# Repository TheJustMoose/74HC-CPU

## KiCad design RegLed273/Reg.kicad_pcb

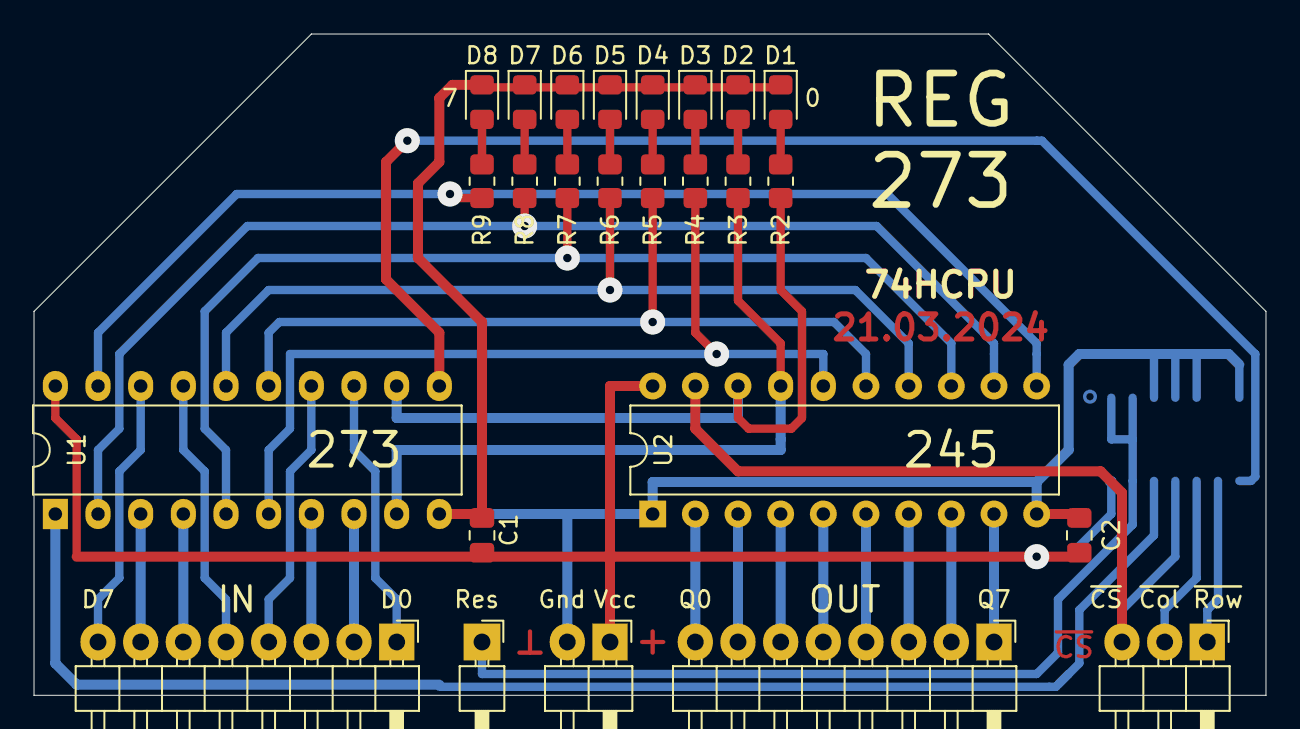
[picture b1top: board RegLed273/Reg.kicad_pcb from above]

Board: 2 copper layers, 73.3 x 39.4 mm, 26 parts (1 on the bottom side), 40 nets.

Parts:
C1, C2: 0.1uF; C_0805_2012Metric_Pad1.18x1.45mm_HandSolder
D1, D2, D3, D4, D5, D6, D7, D8: LED; LED_0805_2012Metric_Pad1.15x1.40mm_HandSolder
J1, J2: Conn_01x08_Male; PinHeader_1x08_P2.54mm_Horizontal
J3: Conn_01x02_Male; PinHeader_1x02_P2.54mm_Horizontal
J4: Conn_01x03_Male; PinHeader_1x03_P2.54mm_Horizontal
J5: Conn_01x01_Male; PinHeader_1x01_P2.54mm_Horizontal
R2, R3, R4, R5, R6, R7, R8, R9: 1k; R_0805_2012Metric_Pad1.20x1.40mm_HandSolder
U1: 74HC273; DIP-20_W7.62mm
U2: 74HC245; DIP-20_W7.62mm
U3: 74LS27; SO-14_3.9x8.65mm_P1.27mm

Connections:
/D0: J1.1, U1.13
/D1: J1.2, U1.8
/D2: J1.3, U1.7
/D3: J1.4, U1.14
/D4: J1.5, U1.17
/D5: J1.6, U1.4
/D6: J1.7, U1.3
/D7: J1.8, U1.18
/L0: R2.1, U1.12, U2.18
/L1: R3.1, U1.9, U2.17
/L2: R4.1, U1.6, U2.16
/L3: R5.1, U1.15, U2.15
/L4: R6.1, U1.16, U2.14
/L5: R7.1, U1.5, U2.13
/L6: R8.1, U1.2, U2.12
/L7: R9.1, U1.19, U2.11
/Q0: J2.8, U2.2
/Q1: J2.7, U2.3
/Q2: J2.6, U2.4
/Q3: J2.5, U2.5
/Q4: J2.4, U2.6
/Q5: J2.3, U2.7
/Q6: J2.2, U2.8
/Q7: J2.1, U2.9
/Res: J5.1, U3.1, U3.2, U3.13
/~CS: J4.3, U2.19, U3.11
/~Col: J4.2, U3.10
/~Row: J4.1, U3.9
GND: C1.2, C2.2, D1.1, D2.1, D3.1, D4.1, D5.1, D6.1, D7.1, D8.1, J3.2, U1.10, U2.1, U2.10, U3.3, U3.4, U3.5, U3.7
unnamed: D1.2, R2.2
unnamed: D2.2, R3.2
unnamed: D3.2, R4.2
unnamed: D4.2, R5.2
unnamed: D5.2, R6.2
unnamed: D6.2, R7.2
unnamed: D7.2, R8.2
unnamed: D8.2, R9.2
unnamed: U1.1, U3.12
unnamed: U1.11, U3.8
VCC: C1.1, C2.1, J3.1, U1.20, U2.20, U3.14

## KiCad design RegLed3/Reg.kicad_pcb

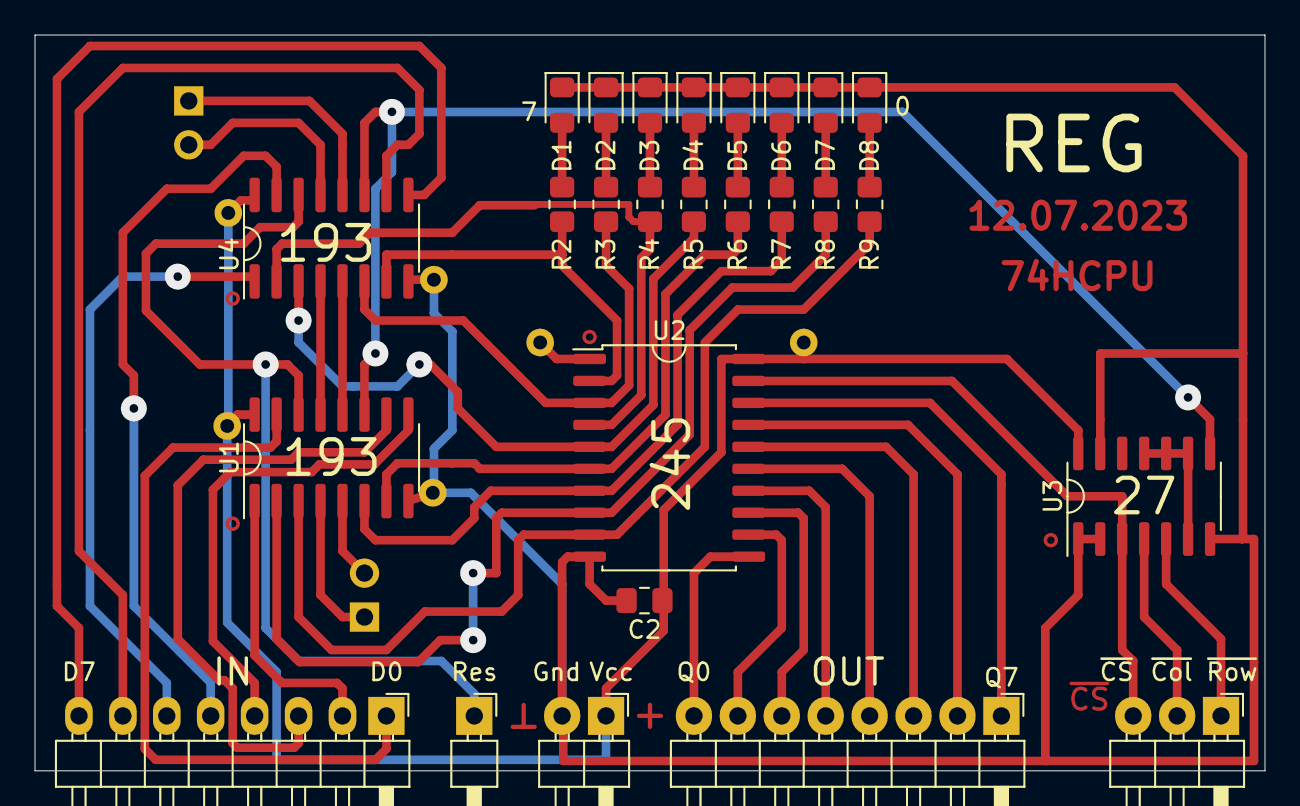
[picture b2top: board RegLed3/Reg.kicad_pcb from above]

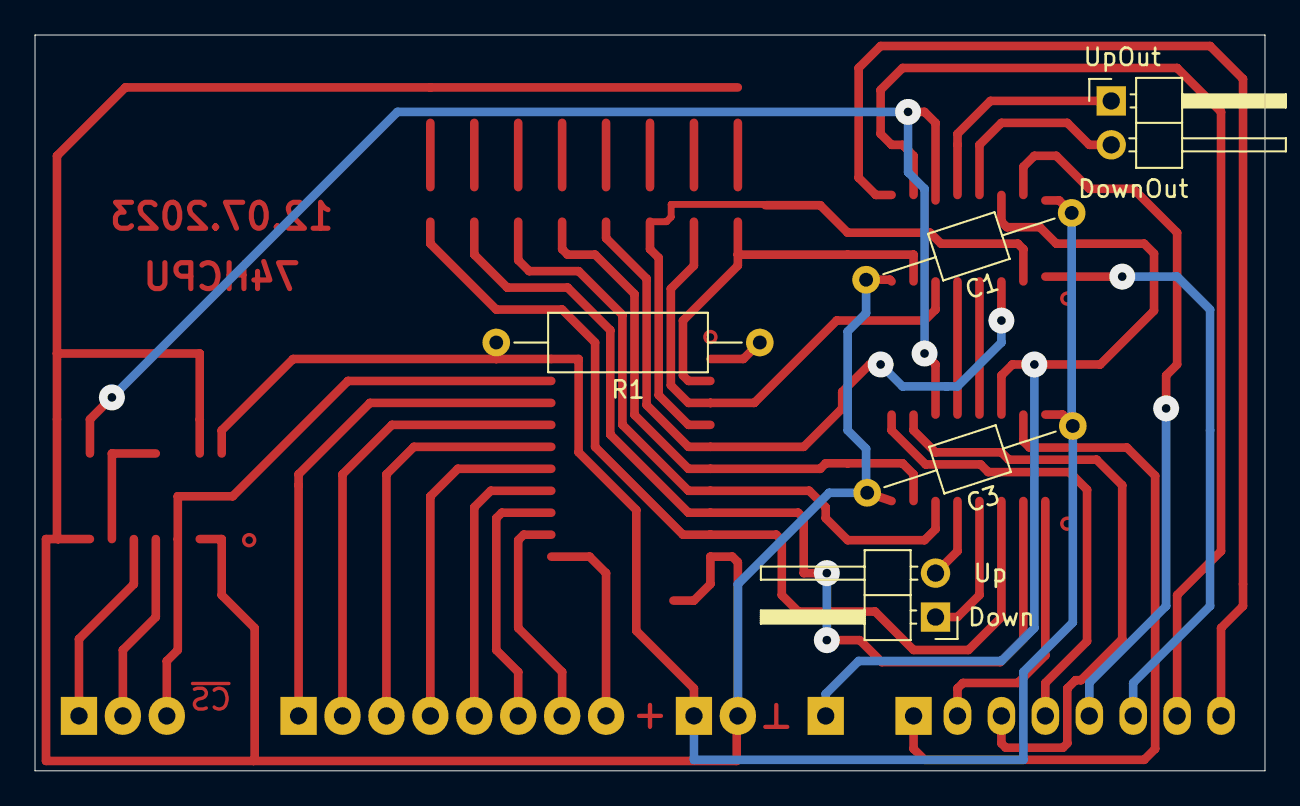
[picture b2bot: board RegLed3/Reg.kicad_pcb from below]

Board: 2 copper layers, 71.1 x 42.5 mm, 31 parts (5 on the bottom side), 47 nets.

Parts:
C1, C3: 0.1uF; C_Axial_L3.8mm_D2.6mm_P12.50mm_Horizontal
C2: 0.1uF; C_0805_2012Metric_Pad1.18x1.45mm_HandSolder
D1, D2, D3, D4, D5, D6, D7, D8: LED; LED_0805_2012Metric_Pad1.15x1.40mm_HandSolder
J1, J2: Conn_01x08_Male; PinHeader_1x08_P2.54mm_Horizontal
J3, J5, J6: Conn_01x02_Male; PinHeader_1x02_P2.54mm_Horizontal
J4: Conn_01x03_Male; PinHeader_1x03_P2.54mm_Horizontal
J7: Conn_01x01_Male; PinHeader_1x01_P2.54mm_Horizontal
R1: 10k; R_Axial_DIN0309_L9.0mm_D3.2mm_P15.24mm_Horizontal
R2, R3, R4, R5, R6, R7, R8, R9: 1k; R_0805_2012Metric_Pad1.20x1.40mm_HandSolder
U1, U4: 74LS193; SOP-16_3.9x9.9mm_P1.27mm
U2: 74HC245; SOP-20_7.5x12.8mm_P1.27mm
U3: 74LS27; SO-14_3.9x8.65mm_P1.27mm

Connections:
/D0: J1.1, U1.15
/D1: J1.2, U1.1
/D2: J1.3, U1.10
/D3: J1.4, U1.9
/D4: J1.5, U4.15
/D5: J1.6, U4.1
/D6: J1.7, U4.10
/D7: J1.8, U4.9
/Down: J6.1, U1.4
/DownLH: U1.13, U4.4
/DownOut: J5.2, U4.13
/L0: R9.1, U1.3, U2.9
/L1: R8.1, U1.2, U2.8
/L2: R7.1, U1.6, U2.7
/L3: R6.1, U1.7, U2.6
/L4: R5.1, U2.5, U4.3
/L5: R4.1, U2.4, U4.2
/L6: R3.1, U2.3, U4.6
/L7: R2.1, U2.2, U4.7
/Q0: J2.8, U2.11
/Q1: J2.7, U2.12
/Q2: J2.6, U2.13
/Q3: J2.5, U2.14
/Q4: J2.4, U2.15
/Q5: J2.3, U2.16
/Q6: J2.2, U2.17
/Q7: J2.1, U2.18
/Res: J7.1, U1.14, U4.14
/Up: J6.2, U1.5
/UpLH: U1.12, U4.5
/UpOut: J5.1, U4.12
/~CS: J4.3, U2.19, U3.3
/~Col: J4.2, U3.4
/~LOAD: U1.11, U3.8, U4.11
/~Row: J4.1, U3.5
GND: C1.2, C2.2, C3.2, D1.1, D2.1, D3.1, D4.1, D5.1, D6.1, D7.1, D8.1, J3.2, U1.8, U2.10, U3.1, U3.2, U3.7, U3.13, U4.8
unnamed: D1.2, R2.2
unnamed: D2.2, R3.2
unnamed: D3.2, R4.2
unnamed: D4.2, R5.2
unnamed: D5.2, R6.2
unnamed: D6.2, R7.2
unnamed: D7.2, R8.2
unnamed: D8.2, R9.2
unnamed: R1.1, U2.1
unnamed: U3.6, U3.9, U3.10, U3.11
VCC: C1.1, C2.1, C3.1, J3.1, R1.2, U1.16, U2.20, U3.14, U4.16

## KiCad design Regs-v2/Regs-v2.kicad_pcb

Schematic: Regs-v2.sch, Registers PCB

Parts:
C1: 1uF; C_Disc_D5.0mm_W2.5mm_P5.00mm
C2, C3, C4: 1uF; C_0805_2012Metric_Pad1.18x1.45mm_HandSolder
D1, D2, D3, D4, D5, D6, D7, D8, D9, D10, D11, D12, D13, D14, D15, D16, D17, D18, D19, D20, D21, D22, D23, D24, D25, D26, D27, D28, D29, D30, D31, D32, D33, D34, D35, D36, D37, D38, D39, D40, D41, D42, D43, D44, D45, D46, D47, D48, D49, D50, D51, D52, D53, D54, D55, D56, D57, D58, D59, D60, D61, D62, D63, D64, D65, D66: LED; LED_Rectangular_W5.0mm_H2.0mm
H1, H2, H3, H4, H5: MountingHole; MountingHole_3.2mm_M3
J1, J2, J3, J4, J5, J6, J7, J8, J10, J13: Conn_01x08_Male; PinHeader_1x08_P2.54mm_Vertical
J9: Conn_01x03_Male; PinHeader_1x03_P2.54mm_Vertical
J11, J12, J16: Conn_01x01_Male; PinHeader_1x01_P2.54mm_Vertical
J14: Conn_01x02_Male; PinHeader_1x02_P2.54mm_Vertical
J15: Screw_Terminal_01x02; TerminalBlock_Phoenix_MKDS-1,5-2_1x02_P5.00mm_Horizontal
R1, R5, R7: 10k; R_Axial_DIN0207_L6.3mm_D2.5mm_P7.62mm_Horizontal
R4, R6: 1k; R_Axial_DIN0207_L6.3mm_D2.5mm_P7.62mm_Horizontal
RN1, RN2, RN3, RN4, RN5, RN6, RN7, RN8: R_Network08; R_Array_SIP9
SW1, SW2: SW_Push; SW_PUSH_6mm_H5mm
U1, U2, U3, U4, U5, U6, U7, U8, U9, U10, U11, U12, U13, U14: REG
U15: 74HC02; DIP-14_W7.62mm_Socket
U16: 74LS139; DIP-16_W7.62mm_Socket
U17: 74HC00; DIP-14_W7.62mm_Socket
U18: 74LS10; DIP-14_W7.62mm_Socket

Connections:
/8\16: J11.1, R1.1, U15.8, U15.12
/DH0: J13.1, U8.1 (D0), U9.1 (D0), U10.1 (D0), U11.1 (D0), U12.1 (D0), U13.1 (D0), U14.1 (D0); also elsewhere on the board
/DH1: J13.2, U8.2 (D1), U9.2 (D1), U10.2 (D1), U11.2 (D1), U12.2 (D1), U13.2 (D1), U14.2 (D1); also elsewhere on the board
/DH2: J13.3, U8.3 (D2), U9.3 (D2), U10.3 (D2), U11.3 (D2), U12.3 (D2), U13.3 (D2), U14.3 (D2); also elsewhere on the board
/DH3: J13.4, U8.4 (D3), U9.4 (D3), U10.4 (D3), U11.4 (D3), U12.4 (D3), U13.4 (D3), U14.4 (D3); also elsewhere on the board
/DH4: J13.5, U8.5 (D4), U9.5 (D4), U10.5 (D4), U11.5 (D4), U12.5 (D4), U13.5 (D4), U14.5 (D4); also elsewhere on the board
/DH5: J13.6, U8.6 (D5), U9.6 (D5), U10.6 (D5), U11.6 (D5), U12.6 (D5), U13.6 (D5), U14.6 (D5); also elsewhere on the board
/DH6: J13.7, U8.7 (D6), U9.7 (D6), U10.7 (D6), U11.7 (D6), U12.7 (D6), U13.7 (D6), U14.7 (D6); also elsewhere on the board
/DH7: J13.8, U8.8 (D7), U9.8 (D7), U10.8 (D7), U11.8 (D7), U12.8 (D7), U13.8 (D7), U14.8 (D7); also elsewhere on the board
/DL1: J10.2, J12.2, U1.2 (D1), U2.2 (D1), U3.2 (D1), U4.2 (D1), U5.2 (D1), U6.2 (D1), U7.2 (D1)
/DL2: J10.3, J12.3, U1.3 (D2), U2.3 (D2), U3.3 (D2), U4.3 (D2), U5.3 (D2), U6.3 (D2), U7.3 (D2)
/DL3: J10.4, J12.4, U1.4 (D3), U2.4 (D3), U3.4 (D3), U4.4 (D3), U5.4 (D3), U6.4 (D3), U7.4 (D3)
/DL4: J10.5, J12.5, U1.5 (D4), U2.5 (D4), U3.5 (D4), U4.5 (D4), U5.5 (D4), U6.5 (D4), U7.5 (D4)
/DL5: J10.6, J12.6, U1.6 (D5), U2.6 (D5), U3.6 (D5), U4.6 (D5), U5.6 (D5), U6.6 (D5), U7.6 (D5)
/DL6: J10.7, J12.7, U1.7 (D6), U2.7 (D6), U3.7 (D6), U4.7 (D6), U5.7 (D6), U6.7 (D6), U7.7 (D6)
/DL7: J10.8, J12.8, U1.8 (D7), U2.8 (D7), U3.8 (D7), U4.8 (D7), U5.8 (D7), U6.8 (D7), U7.8 (D7)
/Latch: J16.1, U15.2, U15.3
/R0.0: D1.2 (A), J1.1, U1.18 (Q0)
/R0.1: D2.2 (A), J1.2, U1.17 (Q1)
/R0.2: D3.2 (A), J1.3, U1.16 (Q2)
/R0.3: D4.2 (A), J1.4, U1.15 (Q3)
/R0.4: D5.2 (A), J1.5, U1.14 (Q4)
/R0.5: D6.2 (A), J1.6, U1.13 (Q5)
/R0.6: D7.2 (A), J1.7, U1.12 (Q6)
/R0.7: D8.2 (A), J1.8, U1.11 (Q7)
/R1.0: D33.2 (A), J5.1, U8.18 (Q0)
/R1.1: D34.2 (A), J5.2, U8.17 (Q1)
/R1.2: D35.2 (A), J5.3, U8.16 (Q2)
/R1.3: D36.2 (A), J5.4, U8.15 (Q3)
/R1.4: D37.2 (A), J5.5, U8.14 (Q4)
/R1.5: D38.2 (A), J5.6, U8.13 (Q5)
/R1.6: D39.2 (A), J5.7, U8.12 (Q6)
/R1.7: D40.2 (A), J5.8, U8.11 (Q7)
/R2.0: D9.2 (A), J2.1, U2.18 (Q0), U3.18 (Q0)
/R2.1: D10.2 (A), J2.2, U2.17 (Q1), U3.17 (Q1)
/R2.2: D11.2 (A), J2.3, U2.16 (Q2), U3.16 (Q2)
/R2.3: D12.2 (A), J2.4, U2.15 (Q3), U3.15 (Q3)
/R2.4: D13.2 (A), J2.5, U2.14 (Q4), U3.14 (Q4)
/R2.5: D14.2 (A), J2.6, U2.13 (Q5), U3.13 (Q5)
/R2.6: D15.2 (A), J2.7, U2.12 (Q6), U3.12 (Q6)
/R2.7: D16.2 (A), J2.8, U2.11 (Q7), U3.11 (Q7)
/R3.0: D41.2 (A), J6.1, U9.18 (Q0), U10.18 (Q0)
/R3.1: D42.2 (A), J6.2, U9.17 (Q1), U10.17 (Q1)
/R3.2: D43.2 (A), J6.3, U9.16 (Q2), U10.16 (Q2)
/R3.3: D44.2 (A), J6.4, U9.15 (Q3), U10.15 (Q3)
/R3.4: D45.2 (A), J6.5, U9.14 (Q4), U10.14 (Q4)
/R3.5: D46.2 (A), J6.6, U9.13 (Q5), U10.13 (Q5)
/R3.6: D47.2 (A), J6.7, U9.12 (Q6), U10.12 (Q6)
/R3.7: D48.2 (A), J6.8, U9.11 (Q7), U10.11 (Q7)
/R4.0: D17.2 (A), J3.1, U4.18 (Q0), U5.18 (Q0)
/R4.1: D18.2 (A), J3.2, U4.17 (Q1), U5.17 (Q1)
/R4.2: D19.2 (A), J3.3, U4.16 (Q2), U5.16 (Q2)
/R4.3: D20.2 (A), J3.4, U4.15 (Q3), U5.15 (Q3)
/R4.4: D21.2 (A), J3.5, U4.14 (Q4), U5.14 (Q4)
/R4.5: D22.2 (A), J3.6, U4.13 (Q5), U5.13 (Q5)
/R4.6: D23.2 (A), J3.7, U4.12 (Q6), U5.12 (Q6)
/R4.7: D24.2 (A), J3.8, U4.11 (Q7), U5.11 (Q7)
/R5.0: D49.2 (A), J7.1, U11.18 (Q0), U12.18 (Q0)
/R5.1: D50.2 (A), J7.2, U11.17 (Q1), U12.17 (Q1)
/R5.2: D51.2 (A), J7.3, U11.16 (Q2), U12.16 (Q2)
/R5.3: D52.2 (A), J7.4, U11.15 (Q3), U12.15 (Q3)
/R5.4: D53.2 (A), J7.5, U11.14 (Q4), U12.14 (Q4)
/R5.5: D54.2 (A), J7.6, U11.13 (Q5), U12.13 (Q5)
/R5.6: D55.2 (A), J7.7, U11.12 (Q6), U12.12 (Q6)
/R5.7: D56.2 (A), J7.8, U11.11 (Q7), U12.11 (Q7)
/R6.0: D25.2 (A), J4.1, U6.18 (Q0), U7.18 (Q0)
/R6.1: D26.2 (A), J4.2, U6.17 (Q1), U7.17 (Q1)
/R6.2: D27.2 (A), J4.3, U6.16 (Q2), U7.16 (Q2)
/R6.3: D28.2 (A), J4.4, U6.15 (Q3), U7.15 (Q3)
/R6.4: D29.2 (A), J4.5, U6.14 (Q4), U7.14 (Q4)
/R6.5: D30.2 (A), J4.6, U6.13 (Q5), U7.13 (Q5)
/R6.6: D31.2 (A), J4.7, U6.12 (Q6), U7.12 (Q6)
/R6.7: D32.2 (A), J4.8, U6.11 (Q7), U7.11 (Q7)
/R7.0: D57.2 (A), J8.1, U13.18 (Q0), U14.18 (Q0)
/R7.1: D58.2 (A), J8.2, U13.17 (Q1), U14.17 (Q1)
/R7.2: D59.2 (A), J8.3, U13.16 (Q2), U14.16 (Q2)
/R7.3: D60.2 (A), J8.4, U13.15 (Q3), U14.15 (Q3)
/R7.4: D61.2 (A), J8.5, U13.14 (Q4), U14.14 (Q4)
/R7.5: D62.2 (A), J8.6, U13.13 (Q5), U14.13 (Q5)
/R7.6: D63.2 (A), J8.7, U13.12 (Q6), U14.12 (Q6)
/R7.7: D64.2 (A), J8.8, U13.11 (Q7), U14.11 (Q7)
/Reg[0]: J9.1, U15.5, U15.6, U15.9
/Reg[1]: J9.2, U16.2 (A0)
/Reg[2]: J9.3, U16.3 (A1)
/~Col0: U1.20 (~Col), U8.20 (~Col), U16.4 (O0)
/~Col1: U2.20 (~Col), U3.20 (~Col), U9.20 (~Col), U10.20 (~Col), U16.5 (O1)
/~Col2: U4.20 (~Col), U5.20 (~Col), U11.20 (~Col), U12.20 (~Col), U16.6 (O2)
/~Col3: U6.20 (~Col), U7.20 (~Col), U13.20 (~Col), U14.20 (~Col), U16.7 (O3)
/~RowH: U8.21 (~Row), U9.21 (~Row), U10.21 (~Row), U11.21 (~Row), U12.21 (~Row), U13.21 (~Row), U14.21 (~Row), U15.10
/~RowL: U1.21 (~Row), U2.21 (~Row), U3.21 (~Row), U4.21 (~Row), U5.21 (~Row), U6.21 (~Row), U7.21 (~Row), U15.13
GND: C1.2, C2.2, C3.2, C4.2, J15.2, R1.2, RN1.1 (common), RN2.1 (common), RN3.1 (common), RN4.1 (common), RN5.1 (common), RN6.1 (common), RN7.1 (common), RN8.1 (common), U1.9 (Gnd), U1.19 (~CS), U2.9 (Gnd), U3.9 (Gnd), U4.9 (Gnd), U5.9 (Gnd), U6.9 (Gnd), U7.9 (Gnd), U8.9 (Gnd), U8.19 (~CS), U9.9 (Gnd), U10.9 (Gnd), U11.9 (Gnd), U12.9 (Gnd), U13.9 (Gnd), U14.9 (Gnd), U15.7 (GND), U16.8 (GND); also elsewhere on the board
unnamed: C1.1, R7.2
unnamed: D1.1 (K), RN1.9 (R8)
unnamed: D2.1 (K), RN1.8 (R7)
unnamed: D3.1 (K), RN1.7 (R6)
unnamed: D4.1 (K), RN1.6 (R5)
unnamed: D5.1 (K), RN1.5 (R4)
unnamed: D6.1 (K), RN1.4 (R3)
unnamed: D7.1 (K), RN1.3 (R2)
unnamed: D8.1 (K), RN1.2 (R1)
unnamed: D9.1 (K), RN2.9 (R8)
unnamed: D10.1 (K), RN2.8 (R7)
unnamed: D11.1 (K), RN2.7 (R6)
unnamed: D12.1 (K), RN2.6 (R5)
unnamed: D13.1 (K), RN2.5 (R4)
unnamed: D14.1 (K), RN2.4 (R3)
unnamed: D15.1 (K), RN2.3 (R2)
unnamed: D16.1 (K), RN2.2 (R1)
unnamed: D17.1 (K), RN3.9 (R8)
unnamed: D18.1 (K), RN3.8 (R7)
unnamed: D19.1 (K), RN3.7 (R6)
unnamed: D20.1 (K), RN3.6 (R5)
unnamed: D21.1 (K), RN3.5 (R4)
unnamed: D22.1 (K), RN3.4 (R3)
unnamed: D23.1 (K), RN3.3 (R2)
unnamed: D24.1 (K), RN3.2 (R1)
unnamed: D25.1 (K), RN4.9 (R8)
unnamed: D26.1 (K), RN4.8 (R7)
unnamed: D27.1 (K), RN4.7 (R6)
unnamed: D28.1 (K), RN4.6 (R5)
unnamed: D29.1 (K), RN4.5 (R4)
unnamed: D30.1 (K), RN4.4 (R3)
unnamed: D31.1 (K), RN4.3 (R2)
unnamed: D32.1 (K), RN4.2 (R1)
unnamed: D33.1 (K), RN5.9 (R8)
unnamed: D34.1 (K), RN5.8 (R7)
unnamed: D35.1 (K), RN5.7 (R6)
unnamed: D36.1 (K), RN5.6 (R5)
unnamed: D37.1 (K), RN5.5 (R4)
unnamed: D38.1 (K), RN5.4 (R3)
unnamed: D39.1 (K), RN5.3 (R2)
unnamed: D40.1 (K), RN5.2 (R1)
unnamed: D41.1 (K), RN6.9 (R8)
unnamed: D42.1 (K), RN6.8 (R7)
unnamed: D43.1 (K), RN6.7 (R6)
unnamed: D44.1 (K), RN6.6 (R5)
unnamed: D45.1 (K), RN6.5 (R4)
unnamed: D46.1 (K), RN6.4 (R3)
unnamed: D47.1 (K), RN6.3 (R2)
unnamed: D48.1 (K), RN6.2 (R1)
unnamed: D49.1 (K), RN7.9 (R8)
unnamed: D50.1 (K), RN7.8 (R7)
unnamed: D51.1 (K), RN7.7 (R6)
unnamed: D52.1 (K), RN7.6 (R5)
unnamed: D53.1 (K), RN7.5 (R4)
unnamed: D54.1 (K), RN7.4 (R3)
unnamed: D55.1 (K), RN7.3 (R2)
unnamed: D56.1 (K), RN7.2 (R1)
unnamed: D57.1 (K), RN8.9 (R8)
unnamed: D58.1 (K), RN8.8 (R7)
unnamed: D59.1 (K), RN8.7 (R6)
unnamed: D60.1 (K), RN8.6 (R5)
unnamed: D61.1 (K), RN8.5 (R4)
unnamed: D62.1 (K), RN8.4 (R3)
unnamed: D63.1 (K), RN8.3 (R2)
unnamed: D64.1 (K), RN8.2 (R1)
unnamed: D65.2 (A), R4.2
unnamed: D66.2 (A), R6.2
unnamed: U15.1, U16.1 (E)
unnamed: U15.4, U15.11
VCC: C2.1, C3.1, C4.1, J15.1, R4.1, R5.1, R6.1, R7.1, U1.10 (Vcc), U2.10 (Vcc), U3.10 (Vcc), U4.10 (Vcc), U5.10 (Vcc), U6.10 (Vcc), U7.10 (Vcc), U8.10 (Vcc), U9.10 (Vcc), U10.10 (Vcc), U11.10 (Vcc), U12.10 (Vcc), U13.10 (Vcc), U14.10 (Vcc), U15.14 (VCC), U16.16 (VCC); also elsewhere on the board

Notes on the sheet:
Bank0
Bank1

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
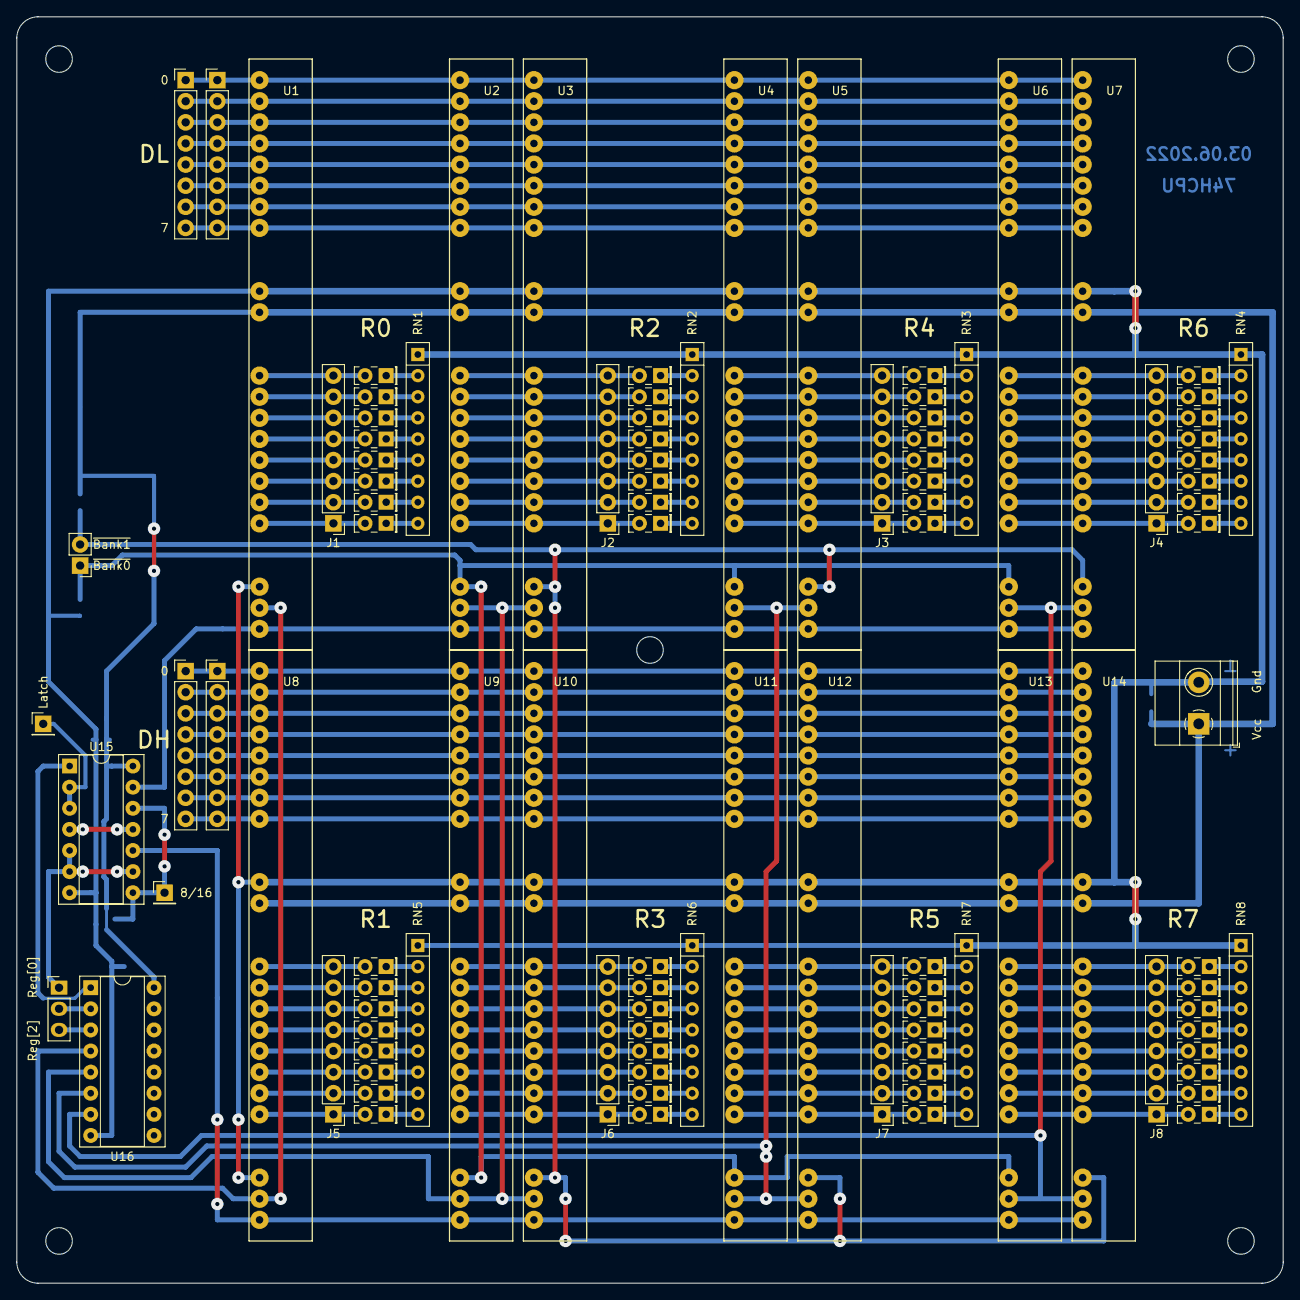
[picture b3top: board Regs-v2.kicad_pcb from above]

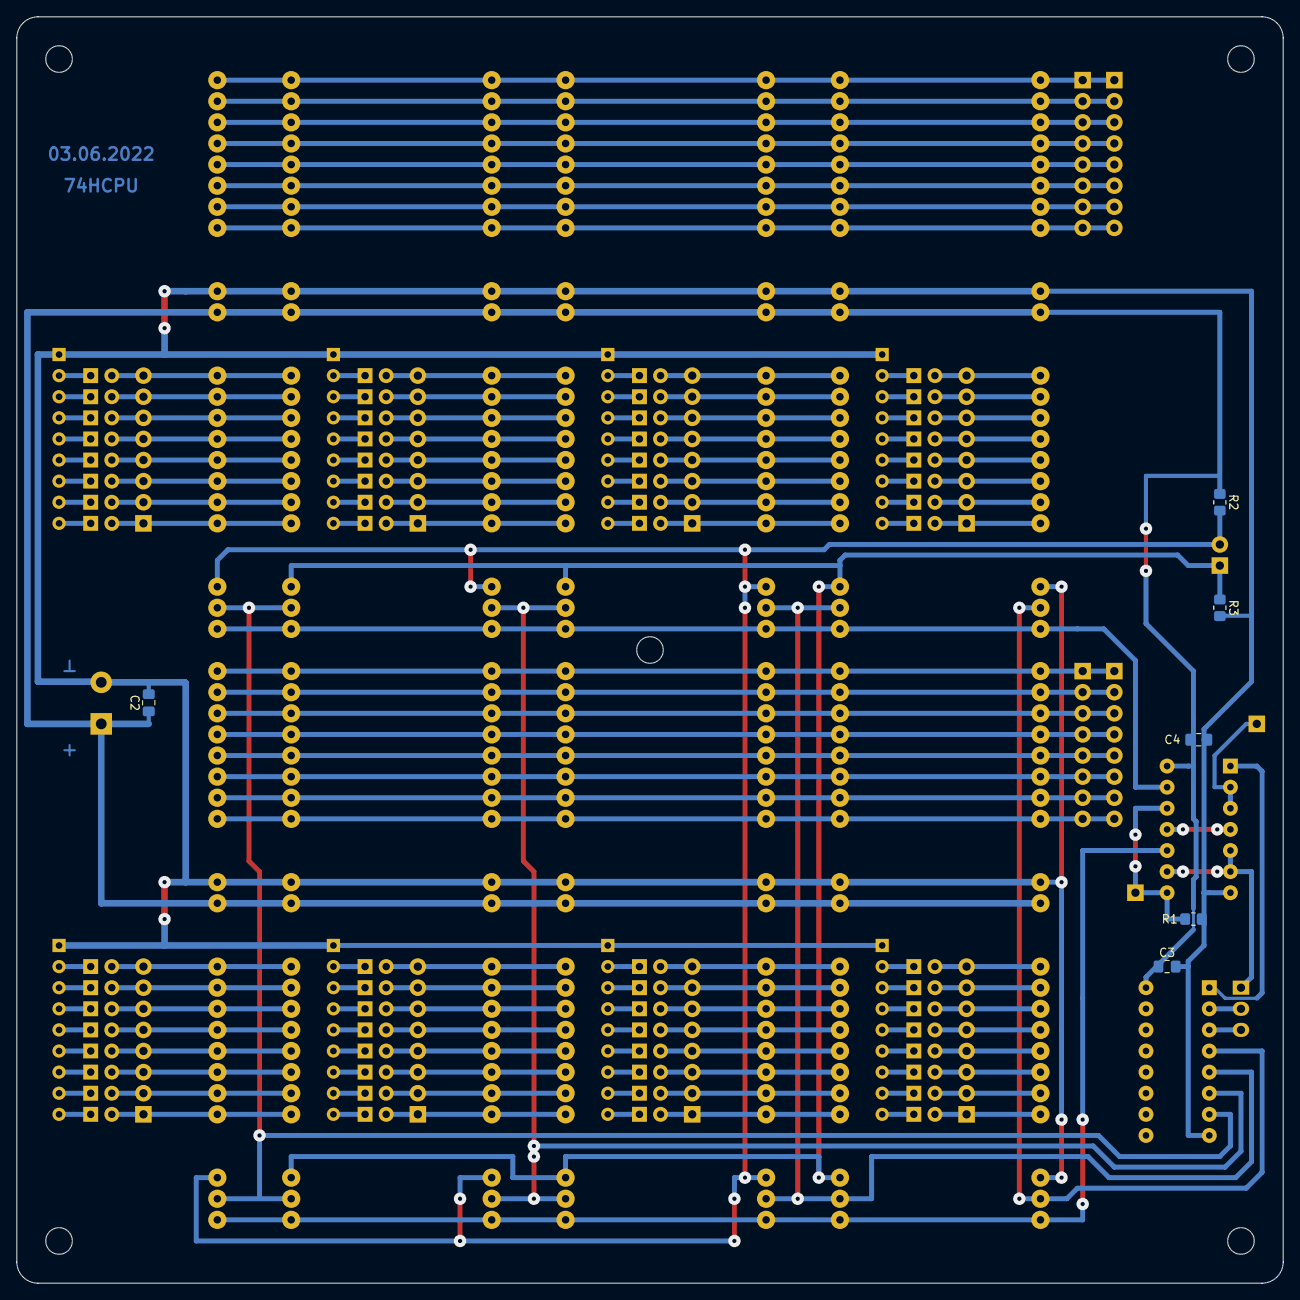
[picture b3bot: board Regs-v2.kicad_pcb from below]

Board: 2 copper layers, 152.4 x 152.4 mm, 116 parts (6 on the bottom side), 161 nets.

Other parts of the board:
J17: Conn_01x08_Male; PinHeader_1x08_P2.54mm_Vertical
R2, R3: 10k; R_0805_2012Metric_Pad1.20x1.40mm_HandSolder

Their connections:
/DH0: J17.1; also elsewhere on the board
/DH1: J17.2; also elsewhere on the board
/DH2: J17.3; also elsewhere on the board
/DH3: J17.4; also elsewhere on the board
/DH4: J17.5; also elsewhere on the board
/DH5: J17.6; also elsewhere on the board
/DH6: J17.7; also elsewhere on the board
/DH7: J17.8; also elsewhere on the board
GND: R3.2; also elsewhere on the board
VCC: R2.1; also elsewhere on the board

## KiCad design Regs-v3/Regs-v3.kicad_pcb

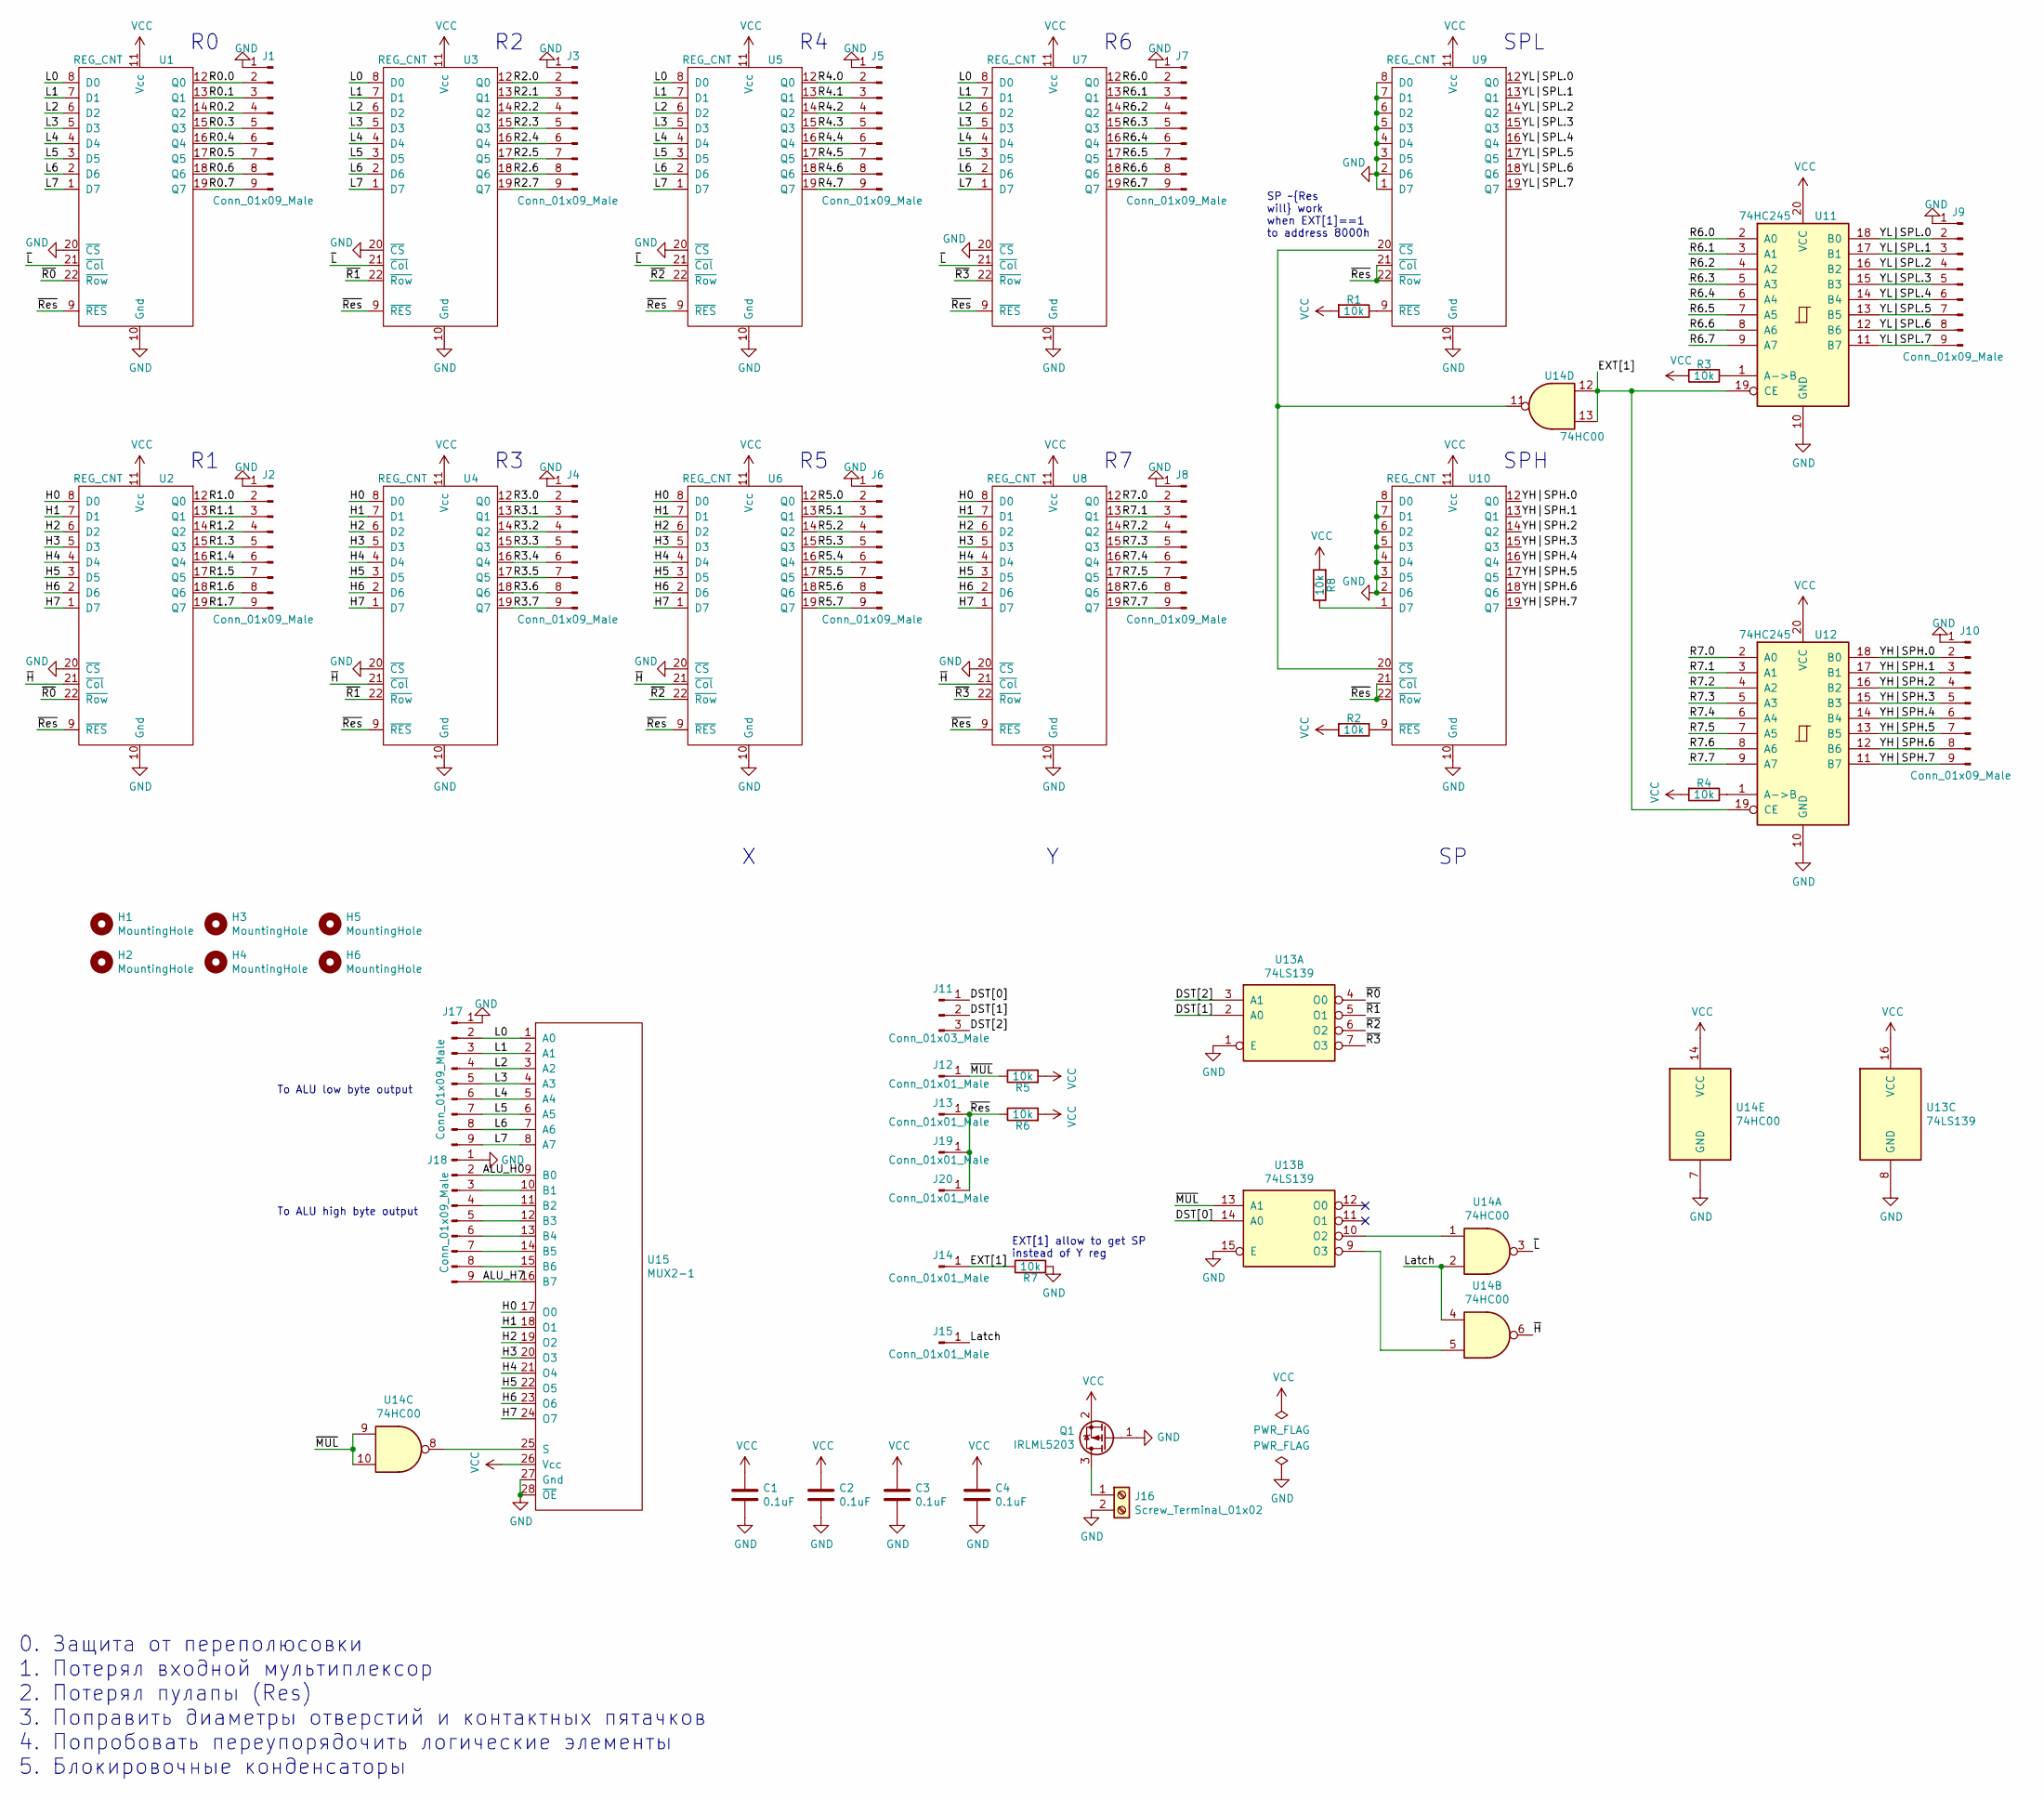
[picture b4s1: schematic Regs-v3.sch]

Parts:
C1, C2, C3, C4: 0.1uF; C_0805_2012Metric_Pad1.18x1.45mm_HandSolder
H1, H2, H3, H4, H5, H6: MountingHole; MountingHole_3.2mm_M3
J1, J2, J3, J4, J5, J6, J7, J8, J9, J10, J17, J18: Conn_01x09_Male; PinHeader_1x09_P2.54mm_Vertical
J11: Conn_01x03_Male; PinHeader_1x03_P2.54mm_Vertical
J12, J13, J14, J15, J19, J20: Conn_01x01_Male; PinHeader_1x01_P2.54mm_Vertical
J16: Screw_Terminal_01x02; TerminalBlock_Phoenix_MKDS-1,5-2_1x02_P5.00mm_Horizontal
Q1: IRLML5203; SOT-23
R1, R2, R3, R4, R5, R6, R7, R8: 10k; R_0805_2012Metric_Pad1.20x1.40mm_HandSolder
U1, U2, U3, U4, U5, U6, U7, U8, U9, U10: REG_CNT
U11, U12: 74HC245; DIP-20_W7.62mm_Socket
U13: 74LS139; DIP-16_W7.62mm_Socket
U14: 74HC00; DIP-14_W7.62mm_Socket
U15: MUX2-1; CMDwoC

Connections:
/ALU_H0: J18.2, U15.9 (B0)
/ALU_H7: J18.9, U15.16 (B7)
/DST[0]: J11.1, U13.14 (A0)
/DST[1]: J11.2, U13.2 (A0)
/DST[2]: J11.3, U13.3 (A1)
/EXT[1]: J14.1, R7.1, U11.19 (CE), U12.19 (CE), U14.12, U14.13
/H0: U2.8 (D0), U4.8 (D0), U6.8 (D0), U8.8 (D0), U15.17 (O0)
/H1: U2.7 (D1), U4.7 (D1), U6.7 (D1), U8.7 (D1), U15.18 (O1)
/H2: U2.6 (D2), U4.6 (D2), U6.6 (D2), U8.6 (D2), U15.19 (O2)
/H3: U2.5 (D3), U4.5 (D3), U6.5 (D3), U8.5 (D3), U15.20 (O3)
/H4: U2.4 (D4), U4.4 (D4), U6.4 (D4), U8.4 (D4), U15.21 (O4)
/H5: U2.3 (D5), U4.3 (D5), U6.3 (D5), U8.3 (D5), U15.22 (O5)
/H6: U2.2 (D6), U4.2 (D6), U6.2 (D6), U8.2 (D6), U15.23 (O6)
/H7: U2.1 (D7), U4.1 (D7), U6.1 (D7), U8.1 (D7), U15.24 (O7)
/L0: J17.2, U1.8 (D0), U3.8 (D0), U5.8 (D0), U7.8 (D0), U15.1 (A0)
/L1: J17.3, U1.7 (D1), U3.7 (D1), U5.7 (D1), U7.7 (D1), U15.2 (A1)
/L2: J17.4, U1.6 (D2), U3.6 (D2), U5.6 (D2), U7.6 (D2), U15.3 (A2)
/L3: J17.5, U1.5 (D3), U3.5 (D3), U5.5 (D3), U7.5 (D3), U15.4 (A3)
/L4: J17.6, U1.4 (D4), U3.4 (D4), U5.4 (D4), U7.4 (D4), U15.5 (A4)
/L5: J17.7, U1.3 (D5), U3.3 (D5), U5.3 (D5), U7.3 (D5), U15.6 (A5)
/L6: J17.8, U1.2 (D6), U3.2 (D6), U5.2 (D6), U7.2 (D6), U15.7 (A6)
/L7: J17.9, U1.1 (D7), U3.1 (D7), U5.1 (D7), U7.1 (D7), U15.8 (A7)
/Latch: J15.1, U14.2, U14.4
/R0.0: J1.2, U1.12 (Q0)
/R0.1: J1.3, U1.13 (Q1)
/R0.2: J1.4, U1.14 (Q2)
/R0.3: J1.5, U1.15 (Q3)
/R0.4: J1.6, U1.16 (Q4)
/R0.5: J1.7, U1.17 (Q5)
/R0.6: J1.8, U1.18 (Q6)
/R0.7: J1.9, U1.19 (Q7)
/R1.0: J2.2, U2.12 (Q0)
/R1.1: J2.3, U2.13 (Q1)
/R1.2: J2.4, U2.14 (Q2)
/R1.3: J2.5, U2.15 (Q3)
/R1.4: J2.6, U2.16 (Q4)
/R1.5: J2.7, U2.17 (Q5)
/R1.6: J2.8, U2.18 (Q6)
/R1.7: J2.9, U2.19 (Q7)
/R2.0: J3.2, U3.12 (Q0)
/R2.1: J3.3, U3.13 (Q1)
/R2.2: J3.4, U3.14 (Q2)
/R2.3: J3.5, U3.15 (Q3)
/R2.4: J3.6, U3.16 (Q4)
/R2.5: J3.7, U3.17 (Q5)
/R2.6: J3.8, U3.18 (Q6)
/R2.7: J3.9, U3.19 (Q7)
/R3.0: J4.2, U4.12 (Q0)
/R3.1: J4.3, U4.13 (Q1)
/R3.2: J4.4, U4.14 (Q2)
/R3.3: J4.5, U4.15 (Q3)
/R3.4: J4.6, U4.16 (Q4)
/R3.5: J4.7, U4.17 (Q5)
/R3.6: J4.8, U4.18 (Q6)
/R3.7: J4.9, U4.19 (Q7)
/R4.0: J5.2, U5.12 (Q0)
/R4.1: J5.3, U5.13 (Q1)
/R4.2: J5.4, U5.14 (Q2)
/R4.3: J5.5, U5.15 (Q3)
/R4.4: J5.6, U5.16 (Q4)
/R4.5: J5.7, U5.17 (Q5)
/R4.6: J5.8, U5.18 (Q6)
/R4.7: J5.9, U5.19 (Q7)
/R5.0: J6.2, U6.12 (Q0)
/R5.1: J6.3, U6.13 (Q1)
/R5.2: J6.4, U6.14 (Q2)
/R5.3: J6.5, U6.15 (Q3)
/R5.4: J6.6, U6.16 (Q4)
/R5.5: J6.7, U6.17 (Q5)
/R5.6: J6.8, U6.18 (Q6)
/R5.7: J6.9, U6.19 (Q7)
/R6.0: J7.2, U7.12 (Q0), U11.2 (A0)
/R6.1: J7.3, U7.13 (Q1), U11.3 (A1)
/R6.2: J7.4, U7.14 (Q2), U11.4 (A2)
/R6.3: J7.5, U7.15 (Q3), U11.5 (A3)
/R6.4: J7.6, U7.16 (Q4), U11.6 (A4)
/R6.5: J7.7, U7.17 (Q5), U11.7 (A5)
/R6.6: J7.8, U7.18 (Q6), U11.8 (A6)
/R6.7: J7.9, U7.19 (Q7), U11.9 (A7)
/R7.0: J8.2, U8.12 (Q0), U12.2 (A0)
/R7.1: J8.3, U8.13 (Q1), U12.3 (A1)
/R7.2: J8.4, U8.14 (Q2), U12.4 (A2)
/R7.3: J8.5, U8.15 (Q3), U12.5 (A3)
/R7.4: J8.6, U8.16 (Q4), U12.6 (A4)
/R7.5: J8.7, U8.17 (Q5), U12.7 (A5)
/R7.6: J8.8, U8.18 (Q6), U12.8 (A6)
/R7.7: J8.9, U8.19 (Q7), U12.9 (A7)
/YH|SPH.0: J10.2, U10.12 (Q0), U12.18 (B0)
/YH|SPH.1: J10.3, U10.13 (Q1), U12.17 (B1)
/YH|SPH.2: J10.4, U10.14 (Q2), U12.16 (B2)
/YH|SPH.3: J10.5, U10.15 (Q3), U12.15 (B3)
/YH|SPH.4: J10.6, U10.16 (Q4), U12.14 (B4)
/YH|SPH.5: J10.7, U10.17 (Q5), U12.13 (B5)
/YH|SPH.6: J10.8, U10.18 (Q6), U12.12 (B6)
/YH|SPH.7: J10.9, U10.19 (Q7), U12.11 (B7)
/YL|SPL.0: J9.2, U9.12 (Q0), U11.18 (B0)
/YL|SPL.1: J9.3, U9.13 (Q1), U11.17 (B1)
/YL|SPL.2: J9.4, U9.14 (Q2), U11.16 (B2)
/YL|SPL.3: J9.5, U9.15 (Q3), U11.15 (B3)
/YL|SPL.4: J9.6, U9.16 (Q4), U11.14 (B4)
/YL|SPL.5: J9.7, U9.17 (Q5), U11.13 (B5)
/YL|SPL.6: J9.8, U9.18 (Q6), U11.12 (B6)
/YL|SPL.7: J9.9, U9.19 (Q7), U11.11 (B7)
/~H: U2.21 (~Col), U4.21 (~Col), U6.21 (~Col), U8.21 (~Col), U14.6
/~L: U1.21 (~Col), U3.21 (~Col), U5.21 (~Col), U7.21 (~Col), U14.3
/~MUL: J12.1, R5.1, U13.13 (A1), U14.9, U14.10
/~R0: U1.22 (~Row), U2.22 (~Row), U13.4 (O0)
/~R1: U3.22 (~Row), U4.22 (~Row), U13.5 (O1)
/~R2: U5.22 (~Row), U6.22 (~Row), U13.6 (O2)
/~R3: U7.22 (~Row), U8.22 (~Row), U13.7 (O3)
/~Res: J13.1, J19.1, J20.1, R6.1, U1.9 (~RES), U2.9 (~RES), U3.9 (~RES), U4.9 (~RES), U5.9 (~RES), U6.9 (~RES), U7.9 (~RES), U8.9 (~RES), U9.21 (~Col), U9.22 (~Row), U10.21 (~Col), U10.22 (~Row)
GND: C1.2, C2.2, C3.2, C4.2, J1.1, J2.1, J3.1, J4.1, J5.1, J6.1, J7.1, J8.1, J9.1, J10.1, J16.2, J17.1, J18.1, Q1.1 (G), R7.2, U1.10 (Gnd), U1.20 (~CS), U2.10 (Gnd), U2.20 (~CS), U3.10 (Gnd), U3.20 (~CS), U4.10 (Gnd), U4.20 (~CS), U5.10 (Gnd), U5.20 (~CS), U6.10 (Gnd), U6.20 (~CS), U7.10 (Gnd), U7.20 (~CS), U8.10 (Gnd), U8.20 (~CS), U9.1 (D7), U9.2 (D6), U9.3 (D5), U9.4 (D4), U9.5 (D3), U9.6 (D2), U9.7 (D1), U9.8 (D0), U9.10 (Gnd), U10.2 (D6), U10.3 (D5), U10.4 (D4), U10.5 (D3), U10.6 (D2), U10.7 (D1), U10.8 (D0), U10.10 (Gnd), U11.10 (GND), U12.10 (GND), U13.1 (E), U13.8 (GND), U13.15 (E), U14.7 (GND), U15.27 (Gnd), U15.28 (~OE)
unnamed: J16.1, Q1.3 (D)
unnamed: J18.3, U15.10 (B1)
unnamed: J18.4, U15.11 (B2)
unnamed: J18.5, U15.12 (B3)
unnamed: J18.6, U15.13 (B4)
unnamed: J18.7, U15.14 (B5)
unnamed: J18.8, U15.15 (B6)
unnamed: R1.1, U9.9 (~RES)
unnamed: R2.1, U10.9 (~RES)
unnamed: R3.1, U11.1 (A->B)
unnamed: R4.1, U12.1 (A->B)
unnamed: R8.1, U10.1 (D7)
unnamed: U9.20 (~CS), U10.20 (~CS), U14.11
unnamed: U13.9 (O3), U14.5
unnamed: U13.10 (O2), U14.1
unnamed: U14.8, U15.25 (S)
VCC: C1.1, C2.1, C3.1, C4.1, Q1.2 (S), R1.2, R2.2, R3.2, R4.2, R5.2, R6.2, R8.2, U1.11 (Vcc), U2.11 (Vcc), U3.11 (Vcc), U4.11 (Vcc), U5.11 (Vcc), U6.11 (Vcc), U7.11 (Vcc), U8.11 (Vcc), U9.11 (Vcc), U10.11 (Vcc), U11.20 (VCC), U12.20 (VCC), U13.16 (VCC), U14.14 (VCC), U15.26 (Vcc)

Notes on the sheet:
SPL
SPH
0. Защита от переполюсовки 1. Потерял входной мультиплексор 2. Потерял пулапы (Res) 3. Поправить диаметры отверстий и контактных пятачков 4. Попробовать переупорядочить логические элементы 5. Блокировочные конденсаторы
To ALU low byte output
To ALU high byte output
EXT[1] allow to get SP instead of Y reg
SP ~Res will work when EXT[1]==1 to address 8000h
